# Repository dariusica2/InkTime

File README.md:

# InkTime Smartwatch – Open Source E-Paper Watch

InkTime is an open-source, low-cost smartwatch built around the nRF52840.  
This repository contains the **Hardware design** (schematic, PCB, 3D models, BOM, and manufacturing files).

## Hardware Functionality

### 1. Power Management
- **USB‑C (J4)** provides VBUS (5V) to the **BQ25180** linear charger.
- **BQ25180** charges a single‑cell Li‑Po battery (connected via test pads `TP_VBAT` / `TP_BAT_GND`).  
  It outputs **SYS** (≈4.4V) which feeds the **RT6160** buck‑boost.
- **RT6160AWSC** (I²C programmable) generates a regulated **3.3V** rail for the whole system.  
  Output set via `VSEL` resistor divider (2.2k / 0.47Ω – jumper configurable).
- **MAX17048** fuel gauge monitors battery voltage and reports via I²C (`ALERT` pin interrupts the MCU).

### 2. Main Microcontroller – nRF52840
- 32‑bit ARM Cortex‑M4F, 1MB Flash, 256kB RAM.
- Interfaces used:
  - **USB 2.0** (D+/D‑) via ESD protection (USBLC6‑2).
  - **I²C** (SCL/SDA) for charger, fuel gauge, IMU, haptic driver, and buck‑boost.
  - **SPI** to the e‑paper display (SCK, MOSI, CS, DC, RST, BUSY).
  - **SWD** for programming/debugging (TC2030 connector).
  - **32MHz** crystal for RF and **32.768kHz** crystal for RTC.
  - **GPIOs** for buttons, haptic enable, and interrupt inputs.

### 3. E‑Paper Display (EPD) Interface
- Connected via 24‑pin FPC connector **J1** (Molex 503480‑2400).
- SPI signals: `SCK`, `MOSI` (from nRF52), `CS`, `DC`, `RST`, `BUSY`.
- Power for the e‑paper panel is provided by the **EPD_3V3** rail, switched by a P‑ch MOSFET (`Q1`) driven by `P1.01` (active low).  
  A 10k pull‑up (`R_PWR_EPD`) keeps the display off until the MCU pulls the gate low.
- Decoupling capacitors (1µF) on each power pin of the FPC.

### 4. Sensors & Actuators
- **BMA423** accelerometer (I²C, address configurable via `SDO`).  
  Interrupts: `INT1` → `P0.08`, `INT2` → `P1.08`.  
  VDDIO = 3.3V, VDD = 3.3V.
- **DRV2605** haptic driver (I²C, address 0x5A).  
  Drives a linear resonant actuator (LRA) or eccentric rotating mass (ERM) via `OUT+` / `OUT-`.  
  Enable pin (`EN`) controlled by `P0.12`.  
  Decoupling: 1µF on VDD, 4.7µF on REG.

### 5. User Input
- Three tactile buttons (Up, Enter, Down) connected to `P0.13`, `P0.14`, `P1.02` with internal pull‑ups (external 10k resistors also present).  
  Pins are pulled to GND when pressed.

### 6. Debug & Programming
- **TC2030‑IDC** (Tag‑Connect) footprint provides SWD: `SWDCLK`, `SWDIO`, `SWO`, `RESET`, 3.3V, GND.
- Test points expose all critical signals: `SWDCLK`, `SWDIO`, `SWO`, `RESET`, `SCL`, `SDA`, `3.3V`, `VBAT`, `GND`, `VREG`.

### 7. RF Section
- **2450AT18B100E** chip antenna matched with a **π‑network** (C3, C22, L1, C4).  
- Antenna placed on the board edge, with **PCB cutout underneath** (no ground or traces under antenna area).
- 50Ω impedance matching ensured by discrete L/C values (3.9nH, 1pF, 1pF, 1pF).

### 8. USB Interface
- **USB‑C** connector (KH‑TYPE‑C‑16P) routed to nRF52840 D+/D‑ via **USBLC6‑2** ESD protection.
- CC lines pulled down with 5.1k resistors for source‑detection (host mode).
- Shield connected to GND.

## Compliance & Design Rules

The PCB was designed with the following constraints (verified by DRC):

| Rule | Notes |
|------|-------|
| **Components on TOP only** | No components on bottom side |
| **4‑layer board** | Top + Power + Bottom routing with Ground pour on GND layer |
| **Power trace width** | 0.3mm |
| **Signal trace width** | 0.15mm |
| **No right‑angle traces** | 45° or curved corners only |
| **Decoupling caps near ICs** | 100nF within 2mm of each power pin |
| **Antenna keep‑out** | No ground or traces under antenna (cutout on PCB) |
| **Via stitching** | Multiple vias between TOP and BOTTOM ground planes, especially near RF |
| **ERC** | Only "Only INPUT pins on NET ID" warnings ignored (by design) |
| **DRC** | Using JLCPCB 2‑layer rules (clearance 5mil, min drill 0.2mm) |
| **Silkscreen** | Component names only (no values), readable, test points labeled |
| **Mechanical fit** | PCB fits into provided enclosure, USB and buttons align |

## Design Decisions & Known Issues

### Accepted DRC/ERC warnings
- **“Only INPUT pins on NET ID”** – ignored as per project guidelines.
- **Dimension errors** caused by USB‑C connector and buttons extending slightly beyond board outline are **ignored** (they fit inside the given enclosure).
- **Silkscreen overlaps** on small 0201 components – unavoidable due to density; names still legible.

### Routing choices
- **Power lines** traces are 0.3mm to handle charging current.
- **Via uses** on 4‑layer board – only used for transitioning between layers when unavoidable.

### Battery connection
- The Li‑Po cell is soldered directly to two test pads (`TP_VBAT`, `TP_BAT_GND`) – no JST connector, saving space.

### Review feedback (DVT stage)
- **Issue resolved**: PCB under antenna not cropped - corpped PCB under antenna
- **Issue resolved**: right angles in routing - using 45 degree angles
- **Issue resolved**: antenna keep‑out area not fully cleared - added via ground stitching around the antenna path

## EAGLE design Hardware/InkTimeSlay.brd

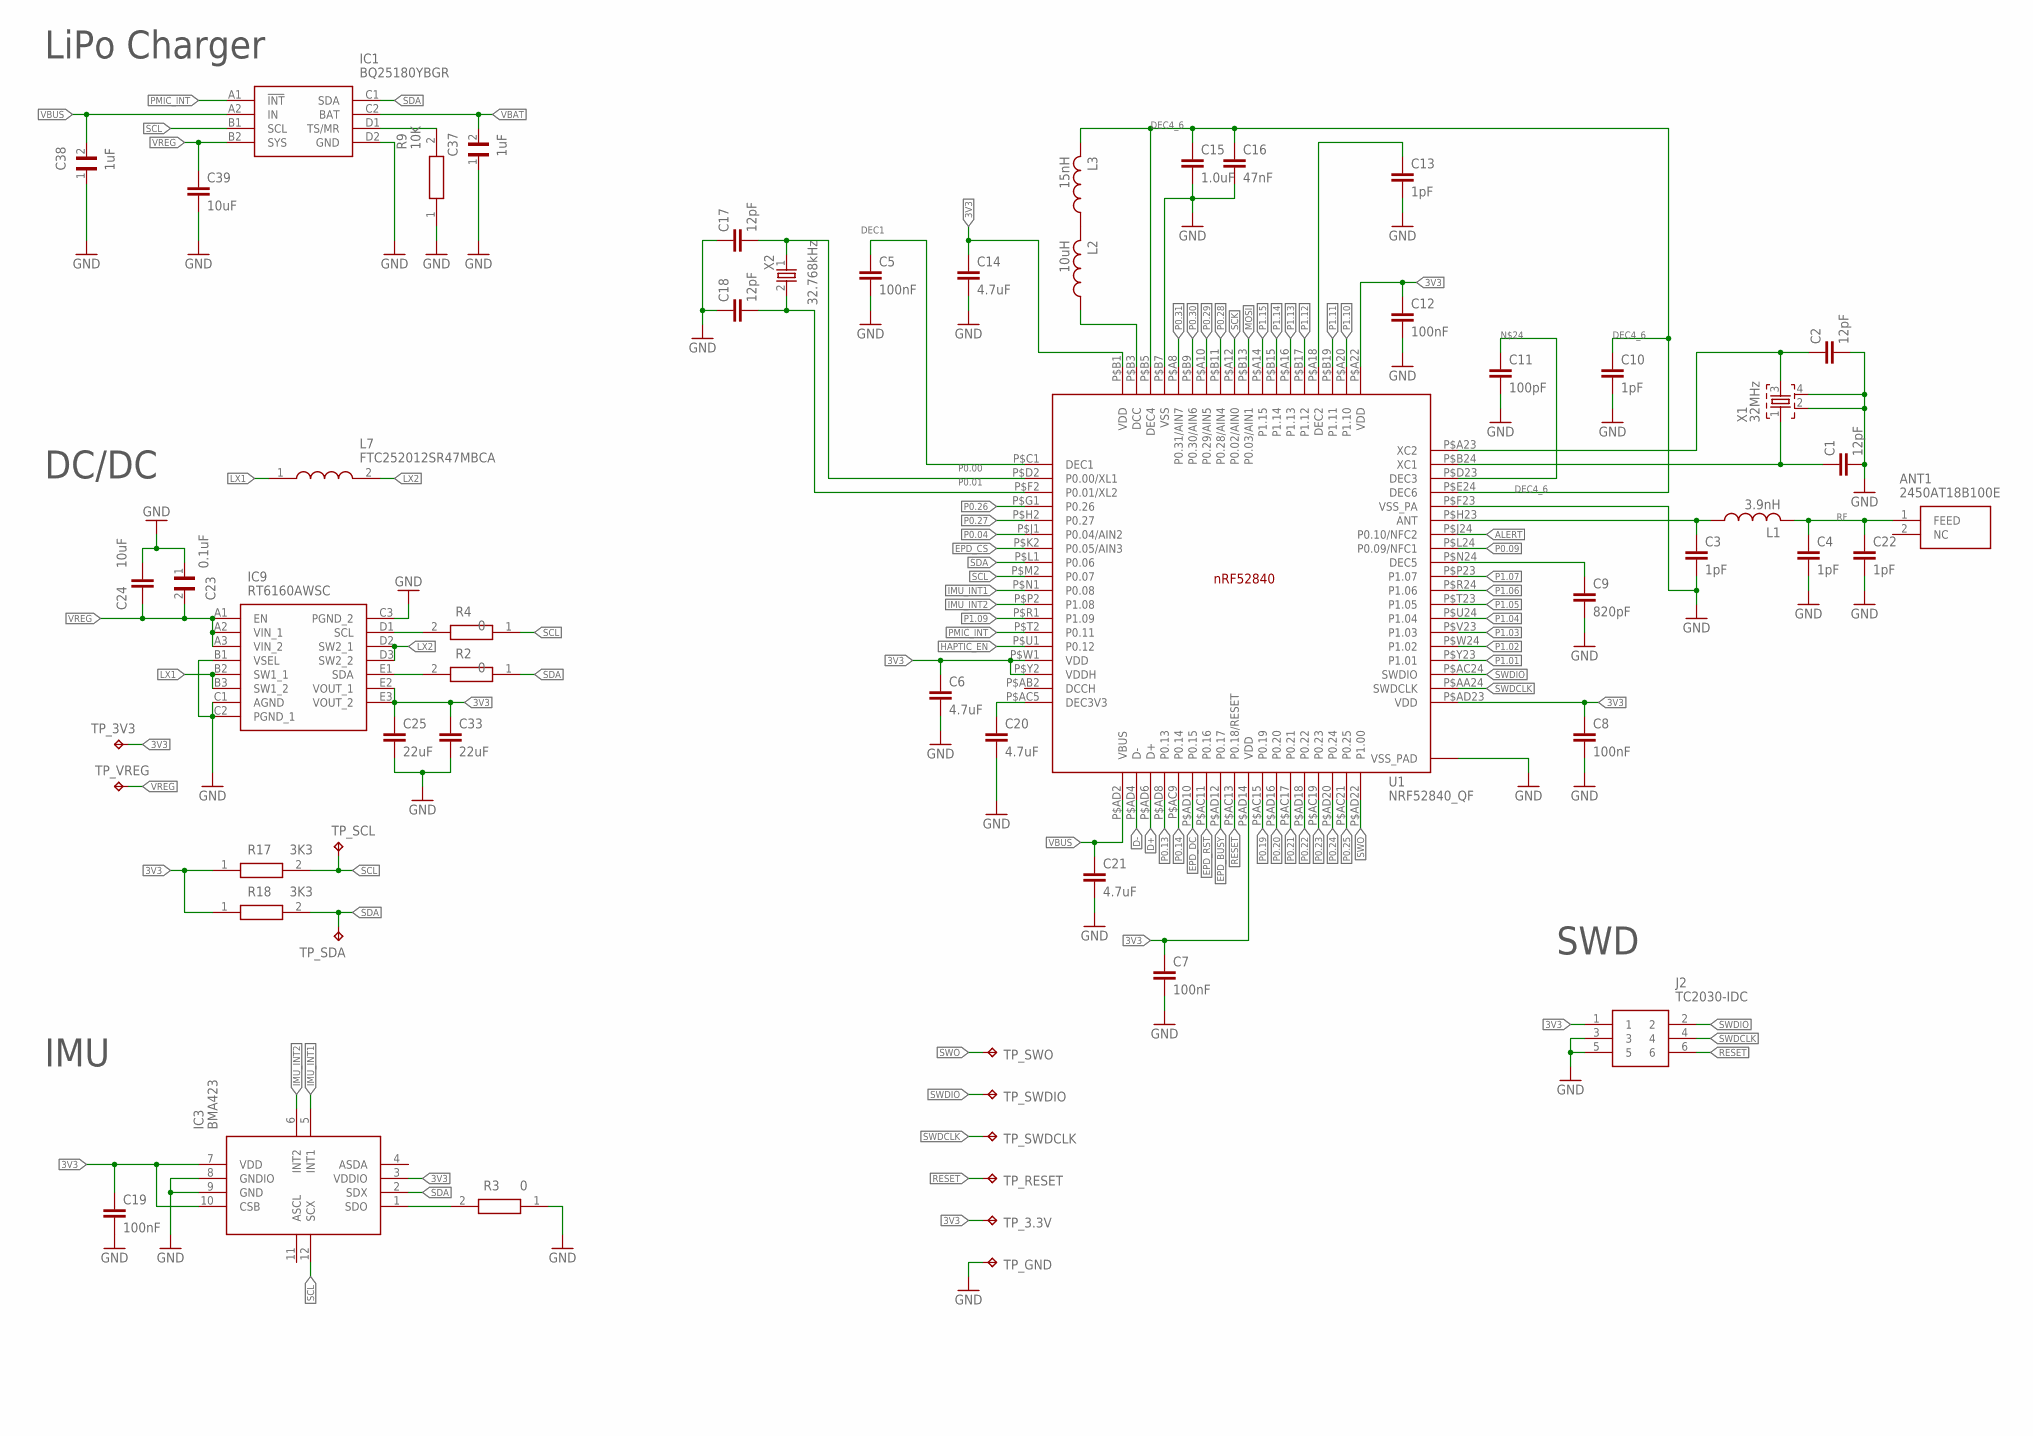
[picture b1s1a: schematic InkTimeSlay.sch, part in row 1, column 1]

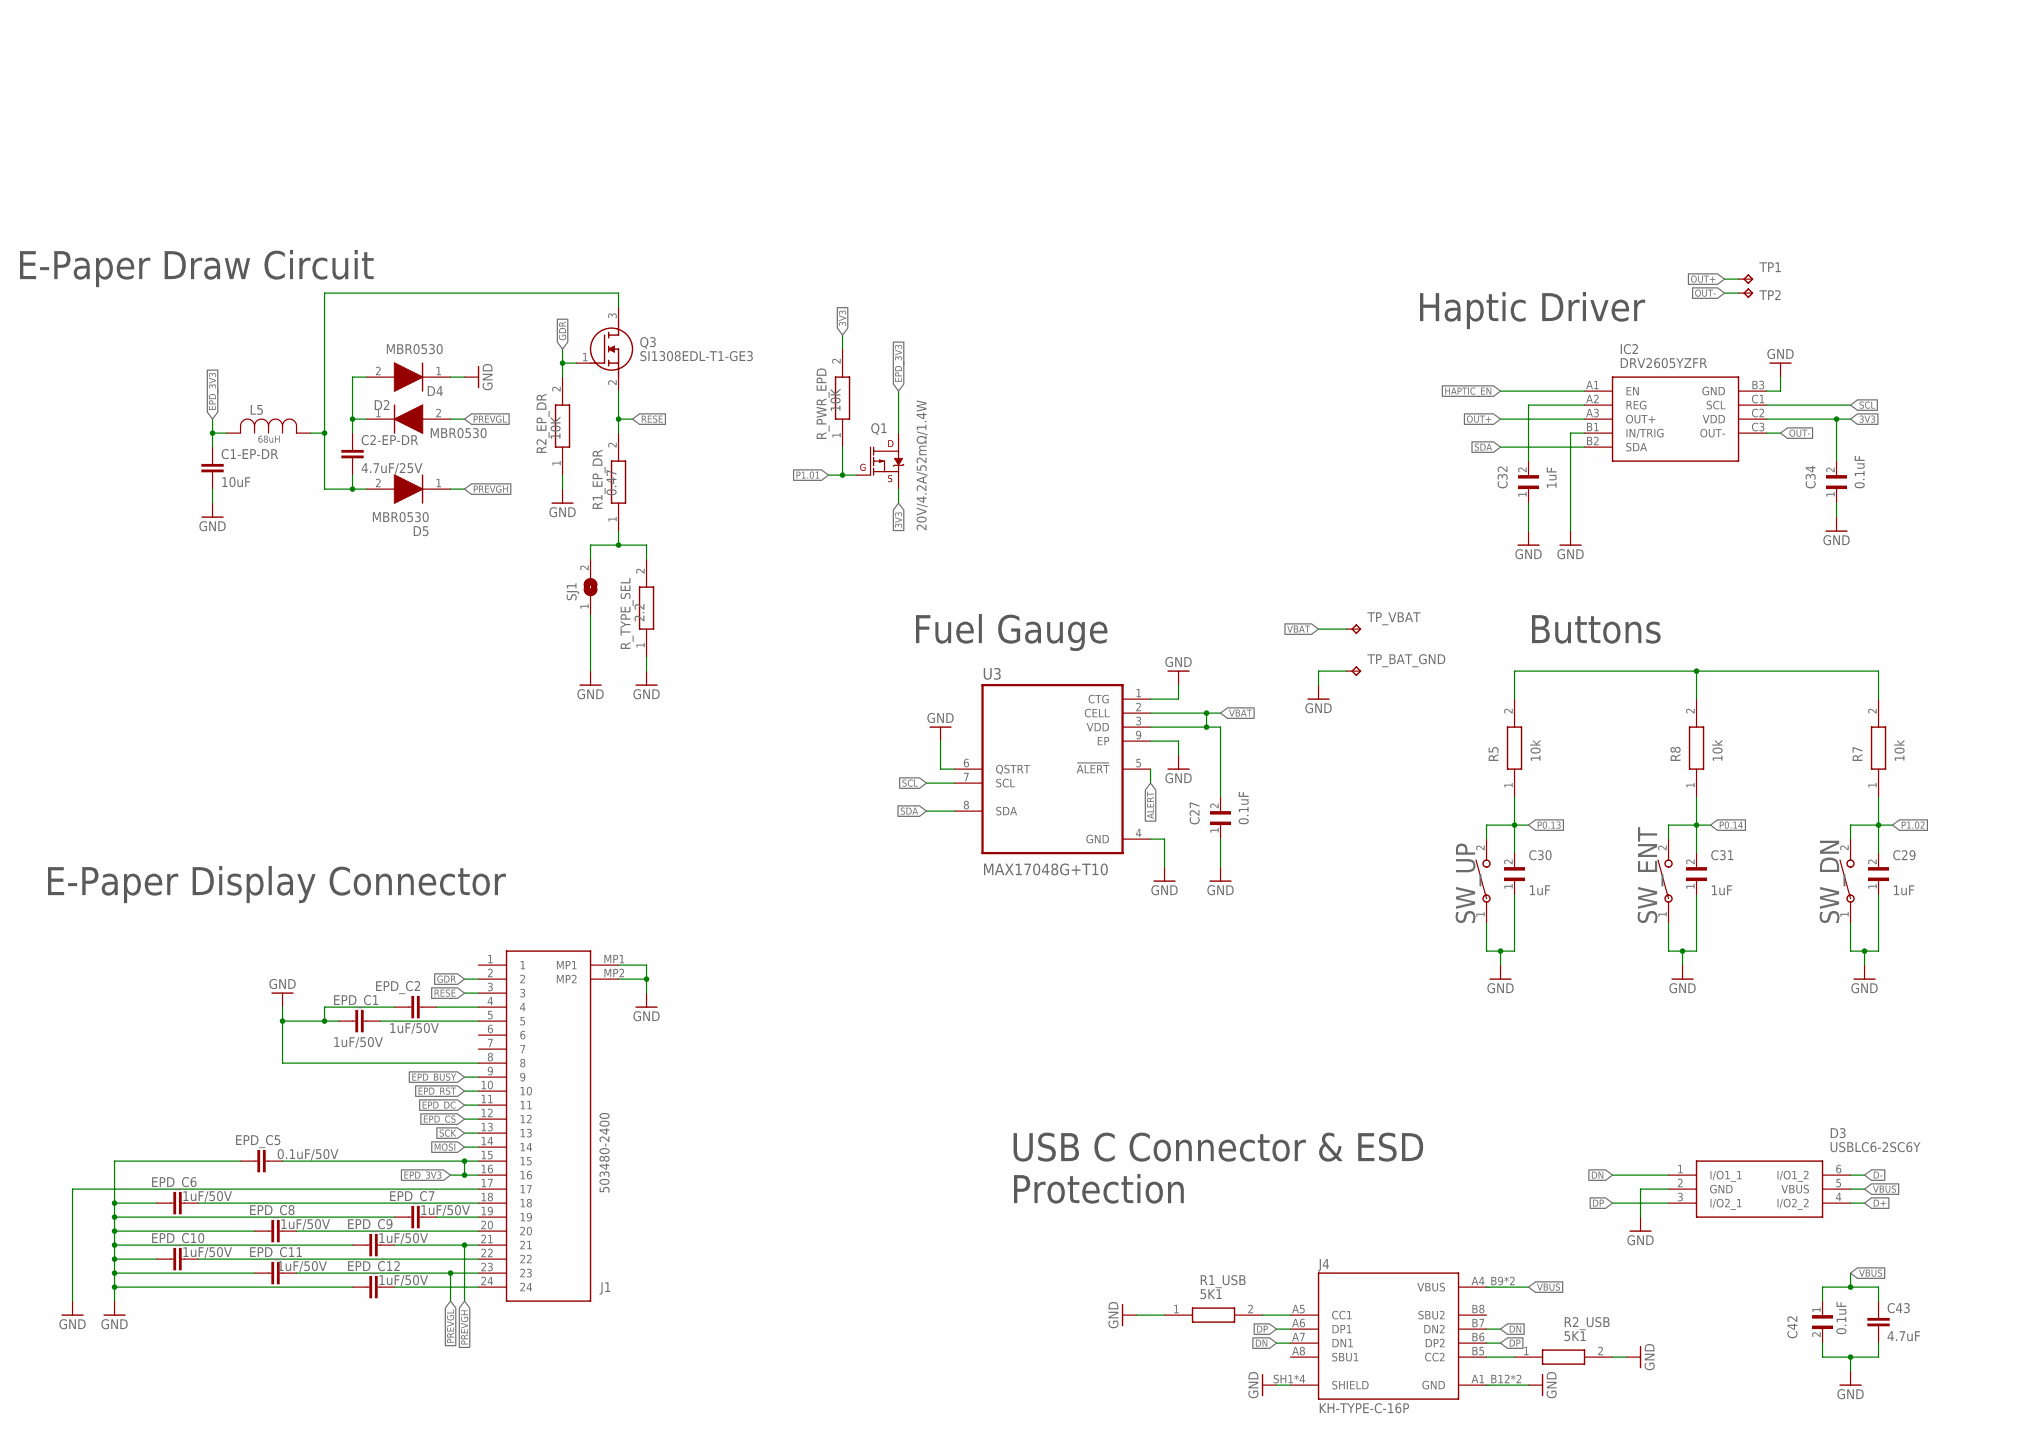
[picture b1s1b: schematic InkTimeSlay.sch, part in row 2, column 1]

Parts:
ANT1: 2450AT18B100E; 2450AT18B100E_ANTC3216X140N
C1, C2, C17, C18: 12pF; NORDIC_NRF_3_RESC0201_L
C1-EP-DR, C24, C39: 10uF; NORDIC_NRF_3_RESC0402_L
C2-EP-DR: 4.7uF/25V; NORDIC_NRF_3_RESC0402_L
C3, C4, C10, C13, C22: 1pF; NORDIC_NRF_3_RESC0201_L
C5, C7, C8, C12, C19: 100nF; NORDIC_NRF_3_RESC0201_L
C6, C14, C20, C21, C43: 4.7uF; NORDIC_NRF_3_RESC0402_L
C9: 820pF; NORDIC_NRF_3_RESC0201_L
C11: 100pF; NORDIC_NRF_3_RESC0201_L
C15: 1.0uF; NORDIC_NRF_3_RESC0402_L
C16: 47nF; NORDIC_NRF_3_RESC0201_L
C23, C27, C34, C42: 0.1uF; GRM011R60J152KE01L_2_CAPC0201X13N
C25, C33: 22uF; NORDIC_NRF_3_RESC0402_L
C29, C30, C31, C32, C37, C38: 1uF; GRM011R60J152KE01L_2_CAPC0201X13N
D2, D4, D5: MBR0530; ESP32_C6_LIBRARY_5_SOD3716X135N
D3: USBLC6-2SC6Y; ESP32_C6_LIBRARY_3_SOT95P280X145-6N
EPD_C1, EPD_C2, EPD_C6, EPD_C7, EPD_C8, EPD_C9, EPD_C10, EPD_C11, EPD_C12: 1uF/50V; NORDIC_NRF_3_RESC0402_L
EPD_C5: 0.1uF/50V; NORDIC_NRF_3_RESC0201_L
IC1: BQ25180YBGR; BQ25180YBGR_BGA8C40P2X4_100X155X50
IC2: DRV2605YZFR; DRV2605YZFR_BGA9C50P3X3_144X144X62
IC3: BMA423; BMA423_BMA423
IC9: RT6160AWSC; RT6160AWSC_BGA15C40P3X5_140X230X60
J1: 503480-2400; 503480-2400_5034802400
J2: TC2030-IDC; TC2030-IDC_TC2030IDC
J4: KH-TYPE-C-16P; KH-TYPE-C-16P_KINGHELM_KH-TYPE-C-16P
L1: 3.9nH; NORDIC_NRF_2_RESC0402_L
L2: 10uH; NORDIC_NRF_2_RESC0402_L
L3: 15nH; NORDIC_NRF_2_RESC0402_L
L5: 68uH; ESP32_C6_LIBRARY_2_IND_4828-WE-TPC_WRE
L7: FTC252012SR47MBCA; MLP2016SR47MT0S1_INDC2016X100N
Q1: 20V/4.2A/52mΩ/1.4W; ESP32_C6_LIBRARY_4_ESP32_C6_LIBRARY_4_ESP32_C6_LIBRARY_4_ES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
Q3: SI1308EDL-T1-GE3; ESP32_C6_LIBRARY_6_SOT65P210X110-3N
R1_EP_DR: 0.47; ERA-1AEB3401C_0201
R1_USB, R2_USB: 5K1; ERA-1AEB3401C_0201
R2, R3, R4: 0; ERA-1AEB3401C_0201
R2_EP_DR, R9: 10K; ERA-1AEB3401C_0201
R5, R7, R8: 10k; ERA-1AEB3401C_0201
R17, R18: 3K3; ERA-1AEB3401C_0201
R_PWR_EPD: 10K; ERA-1AEB3401C_0201
R_TYPE_SEL: 2.2; ERA-1AEB3401C_0201
SJ1: ESP32_C6_LIBRARY_7_JUMPER_SJ
SW_DN: 2025-10-22_07-23-44_LIBRARY_EVP-AKE31ASW_EVP-AKE3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; 2025-10-22_07-23-44_LIBRARY_SW_EVP-AKE31A_PAN
SW_ENT: 2025-10-22_07-23-44_LIBRARY_EVP-AKE31ASW_EVP-AKE3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; 2025-10-22_07-23-44_LIBRARY_SW_EVP-AKE31A_PAN
SW_UP: 2025-10-22_07-23-44_LIBRARY_EVP-AKE31ASW_EVP-AKE3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; 2025-10-22_07-23-44_LIBRARY_SW_EVP-AKE31A_PAN
TP1, TP2: HECTOR_WATCH_1_TPTP20R; HECTOR_WATCH_1_TP20R
TP_3.3V, TP_3V3: HECTOR_WATCH_1_TPTP20R; HECTOR_WATCH_1_TP20R
TP_BAT_GND: HECTOR_WATCH_1_TPTP20R; HECTOR_WATCH_1_TP20R
TP_GND: HECTOR_WATCH_1_TPTP20R; HECTOR_WATCH_1_TP20R
TP_RESET: HECTOR_WATCH_1_TPTP20R; HECTOR_WATCH_1_TP20R
TP_SCL: HECTOR_WATCH_1_TPTP20R; HECTOR_WATCH_1_TP20R
TP_SDA: HECTOR_WATCH_1_TPTP20R; HECTOR_WATCH_1_TP20R
TP_SWDCLK: HECTOR_WATCH_1_TPTP20R; HECTOR_WATCH_1_TP20R
TP_SWDIO: HECTOR_WATCH_1_TPTP20R; HECTOR_WATCH_1_TP20R
TP_SWO: HECTOR_WATCH_1_TPTP20R; HECTOR_WATCH_1_TP20R
TP_VBAT: HECTOR_WATCH_1_TPTP20R; HECTOR_WATCH_1_TP20R
TP_VREG: HECTOR_WATCH_1_TPTP20R; HECTOR_WATCH_1_TP20R
U1: NRF52840_QF; NORDIC_NRF_4_AQFN50P700X700X85_HS-74N
U3: MAX17048G+T10; ESP32_C6_LIBRARY_SON50P200X200X80-9N
X1: 32MHz; NORDIC_NRF_BT-XTAL_2016_N
X2: 32.768kHz; NORDIC_NRF_1_XTAL_3215_N

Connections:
3V3: C6.1, C7.1, C8.1, C12.1, C14.1, C19.1, C25.1, C33.1, C34.2, IC2.C2 (VDD), IC3.3 (VDDIO), IC3.7 (VDD), IC3.10 (CSB), IC9.E2 (VOUT_1), IC9.E3 (VOUT_2), J2.1, Q1.2 (S), R17.1, R18.1, R_PWR_EPD.2, TP_3.3V.TP, TP_3V3.TP, U1.P$A22 (VDD), U1.P$AD14 (VDD), U1.P$AD23 (VDD), U1.P$B1 (VDD), U1.P$W1 (VDD), U1.P$Y2 (VDDH)
ALERT: U1.P$J24 (P0.10/NFC2), U3.5 (!ALERT)
D+: D3.4 (I/O2_2), U1.P$AD6 (D+)
D-: D3.6 (I/O1_2), U1.P$AD4 (D-)
DEC1: C5.1, U1.P$C1 (DEC1)
DEC4_6: C10.1, C15.1, C16.1, L3.2, U1.P$B5 (DEC4), U1.P$E24 (DEC6)
DN: D3.1 (I/O1_1), J4.A7 (DN1), J4.B7 (DN2)
DP: D3.3 (I/O2_1), J4.A6 (DP1), J4.B6 (DP2)
EPD_3V3: C1-EP-DR.1, EPD_C5.2, J1.15, J1.16, L5.2, Q1.3 (D)
EPD_BUSY: J1.9, U1.P$AD12 (P0.17)
EPD_CS: J1.12, U1.P$K2 (P0.05/AIN3)
EPD_DC: J1.11, U1.P$AD10 (P0.15)
EPD_RST: J1.10, U1.P$AC11 (P0.16)
GDR: J1.2, Q3.1 (G), R2_EP_DR.2
GND: C1.2, C1-EP-DR.2, C2.2, C3.2, C4.2, C5.2, C6.2, C7.2, C8.2, C9.2, C10.2, C11.2, C12.2, C13.2, C14.2, C15.2, C16.2, C17.1, C18.1, C19.2, C20.2, C21.2, C22.2, C23.1, C24.1, C25.2, C27.1, C29.1, C30.1, C31.1, C32.1, C33.2, C34.1, C37.1, C38.1, C39.2, C42.2, C43.2, D3.2 (GND), D4.1 (K), EPD_C1.1, EPD_C2.1, EPD_C5.1, EPD_C6.1, EPD_C7.1, EPD_C8.1, EPD_C9.1, EPD_C10.1, EPD_C11.1, EPD_C12.1, IC1.D2 (GND), IC2.B1 (IN/TRIG), IC2.B3 (GND), IC3.8 (GNDIO), IC3.9 (GND), IC9.B1 (VSEL), IC9.C1 (AGND), IC9.C2 (PGND_1), IC9.C3 (PGND_2), J1.8, J1.17, J1.MP1, J1.MP2, J2.3, J2.5, J4.A1_B12 (GND), J4.A12_B1 (GND), J4.SH1 (SHIELD), J4.SH2 (SHIELD), J4.SH3 (SHIELD), J4.SH4 (SHIELD), R1_USB.1, R2_EP_DR.1, R2_USB.2, R3.1, R9.1, R_TYPE_SEL.1, SJ1.1, SW_DN.1, SW_ENT.1, SW_UP.1, TP_BAT_GND.TP, TP_GND.TP, U1.P$74 (VSS_PAD), U1.P$75 (VSS_PAD), U1.P$76 (VSS_PAD), U1.P$77 (VSS_PAD), U1.P$78 (VSS_PAD), U1.P$79 (VSS_PAD), U1.P$80 (VSS_PAD), U1.P$81 (VSS_PAD), U1.P$82 (VSS_PAD), U1.P$83 (VSS_PAD), U1.P$84 (VSS_PAD), U1.P$85 (VSS_PAD), U1.P$86 (VSS_PAD), U1.P$87 (VSS_PAD), U1.P$88 (VSS_PAD), U1.P$89 (VSS_PAD), U1.P$90 (VSS_PAD), U1.P$B7 (VSS), U1.P$F23 (VSS_PA), U3.1 (CTG), U3.4 (GND), U3.6 (QSTRT), U3.9 (EP), X1.2, X1.4
HAPTIC_EN: IC2.A1 (EN), U1.P$U1 (P0.12)
IMU_INT1: IC3.5 (INT1), U1.P$N1 (P0.08)
IMU_INT2: IC3.6 (INT2), U1.P$P2 (P1.08)
LX1: IC9.B2 (SW1_1), IC9.B3 (SW1_2), L7.1
LX2: IC9.D2 (SW2_1), IC9.D3 (SW2_2), L7.2
MOSI: J1.14, U1.P$B13 (P0.03/AIN1)
unnamed: C2-EP-DR.2, D5.2 (A), L5.1, Q3.3 (D)
unnamed: L2.2, L3.1
unnamed: IC1.D1 (TS/MR), R9.2
unnamed: C1.1, U1.P$B24 (XC1), X1.1
unnamed: L2.1, U1.P$B3 (DCC)
unnamed: C2-EP-DR.1, D2.1 (K), D4.2 (A)
unnamed: R5.2, R7.2, R8.2
unnamed: C32.2, IC2.A2 (REG)
unnamed: R1_EP_DR.1, R_TYPE_SEL.2, SJ1.2
unnamed: J4.A5 (CC1), R1_USB.2
unnamed: EPD_C2.2, J1.4
unnamed: EPD_C1.2, J1.5
unnamed: C9.1, U1.P$N24 (DEC5)
unnamed: C13.1, U1.P$A18 (DEC2)
unnamed: C20.1, U1.P$AC5 (DEC3V3)
unnamed: IC9.D1 (SCL), R4.2
unnamed: J4.B5 (CC2), R2_USB.1
unnamed: C3.1, L1.1, U1.P$H23 (ANT)
unnamed: IC9.E1 (SDA), R2.2
unnamed: C11.1, U1.P$D23 (DEC3)
unnamed: IC3.1 (SDO), R3.2
unnamed: EPD_C6.2, J1.18
unnamed: EPD_C7.2, J1.19
unnamed: C2.1, U1.P$A23 (XC2), X1.3
unnamed: EPD_C8.2, J1.20
unnamed: EPD_C10.2, J1.22
unnamed: EPD_C12.2, J1.24
OUT+: IC2.A3 (OUT+), TP1.TP
OUT-: IC2.C3 (OUT-), TP2.TP
P0.00: C17.2, U1.P$D2 (P0.00/XL1), X2.1
P0.01: C18.2, U1.P$F2 (P0.01/XL2), X2.2
P0.04: U1.P$J1 (P0.04/AIN2)
P0.09: U1.P$L24 (P0.09/NFC1)
P0.13: C30.2, R5.1, SW_UP.2, U1.P$AD8 (P0.13)
P0.14: C31.2, R8.1, SW_ENT.2, U1.P$AC9 (P0.14)
P0.19: U1.P$AC15 (P0.19)
P0.20: U1.P$AD16 (P0.20)
P0.21: U1.P$AC17 (P0.21)
P0.22: U1.P$AD18 (P0.22)
P0.23: U1.P$AC19 (P0.23)
P0.24: U1.P$AD20 (P0.24)
P0.25: U1.P$AC21 (P0.25)
P0.26: U1.P$G1 (P0.26)
P0.27: U1.P$H2 (P0.27)
P0.28: U1.P$B11 (P0.28/AIN4)
P0.29: U1.P$A10 (P0.29/AIN5)
P0.30: U1.P$B9 (P0.30/AIN6)
P0.31: U1.P$A8 (P0.31/AIN7)
P1.01: Q1.1 (G), R_PWR_EPD.1, U1.P$Y23 (P1.01)
P1.02: C29.2, R7.1, SW_DN.2, U1.P$W24 (P1.02)
P1.03: U1.P$V23 (P1.03)
P1.04: U1.P$U24 (P1.04)
P1.05: U1.P$T23 (P1.05)
P1.06: U1.P$R24 (P1.06)
P1.07: U1.P$P23 (P1.07)
P1.09: U1.P$R1 (P1.09)
P1.10: U1.P$A20 (P1.10)
P1.11: U1.P$B19 (P1.11)
P1.12: U1.P$B17 (P1.12)
P1.13: U1.P$A16 (P1.13)
P1.14: U1.P$B15 (P1.14)
P1.15: U1.P$A14 (P1.15)
PMIC_INT: IC1.A1 (!INT), U1.P$T2 (P0.11)
PREVGH: D5.1 (K), EPD_C9.2, J1.21
PREVGL: D2.2 (A), EPD_C11.2, J1.23
RESE: J1.3, Q3.2 (S), R1_EP_DR.2
RESET: J2.6, TP_RESET.TP, U1.P$AC13 (P0.18/RESET)
RF: ANT1.1 (FEED), C4.1, C22.1, L1.2
SCK: J1.13, U1.P$A12 (P0.02/AIN0)
SCL: IC1.B1 (SCL), IC2.C1 (SCL), IC3.12 (SCX), R4.1, R17.2, TP_SCL.TP, U1.P$M2 (P0.07), U3.7 (SCL)
SDA: IC1.C1 (SDA), IC2.B2 (SDA), IC3.2 (SDX), R2.1, R18.2, TP_SDA.TP, U1.P$L1 (P0.06), U3.8 (SDA)
SWDCLK: J2.4, TP_SWDCLK.TP, U1.P$AA24 (SWDCLK)
SWDIO: J2.2, TP_SWDIO.TP, U1.P$AC24 (SWDIO)
SWO: TP_SWO.TP, U1.P$AD22 (P1.00)
VBAT: C27.2, C37.2, IC1.C2 (BAT), TP_VBAT.TP, U3.2 (CELL), U3.3 (VDD)
VBUS: C21.1, C38.2, C42.1, C43.1, D3.5 (VBUS), IC1.A2 (IN), J4.A4_B9 (VBUS), J4.A9_B4 (VBUS), U1.P$AD2 (VBUS)
VREG: C23.2, C24.2, C39.1, IC1.B2 (SYS), IC9.A1 (EN), IC9.A2 (VIN_1), IC9.A3 (VIN_2), TP_VREG.TP

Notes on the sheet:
LiPo Charger
DC/DC
IMU
SWD
E-Paper Draw Circuit
E-Paper Display Connector
Fuel Gauge
USB C Connector & ESD Protection
Haptic Driver
Buttons

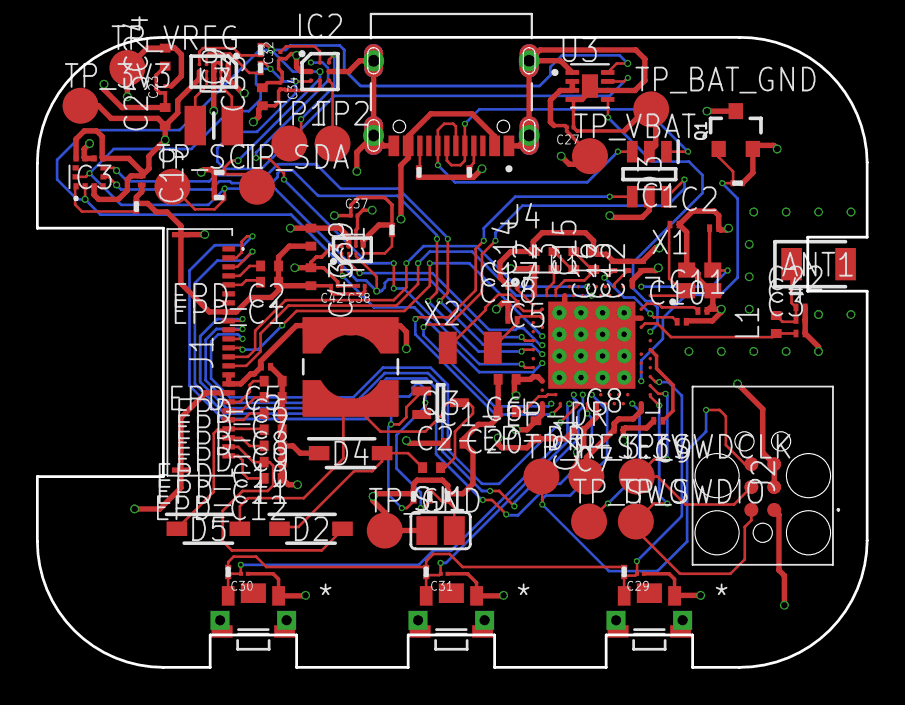
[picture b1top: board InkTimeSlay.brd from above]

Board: 4 copper layers, 46.1 x 35.0 mm, 105 parts (0 on the bottom side), 71 nets.

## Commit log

2026-04-16 Add schematic and board pre-review
2026-04-19 2D PCB changes
    Got rid of 90 degree angles in wire routing, isolated the antenna better and surrounded its premises with GND vias, cropped the board under the antenna
2026-04-22 Add missing components
    Add 3D files, add 3D exploded image, add schematic PDF
2026-04-22 Add Manufacturing folder

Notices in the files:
parts and their libraries:
COPYRIGHT: Copyright (C) 2024 Ultra Librarian. All rights reserved.
COPYRIGHT: Copyright (C) 2025 Ultra Librarian. All rights reserved.
